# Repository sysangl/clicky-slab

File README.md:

The second in the Brick series. Although this one is called a slab cause it's way larger than the other Brick devices.

# Clicky Slab
## The big brother of the [clicky-brick](https://github.com/sysangl/clicky-brick)

A custom keyboard that would probably cause a house fire.

## Why did I make this?
I was bored, and I needed to fix my current keyboard.

## Features
This is a 86-key keyboard, which should have at least 4KRO, using KMK on a Raspberry Pi Pico. The case and keycaps are 3D printed.
It contains all the keys on a normal keyboard without a numpad and the PRINT_SCREEN key. There are an additional 5 keys on the right hand side that can be customised to do whatever you want. By default these would control the KMK keyboard layers.

# Showcase
- PCB designed in KiCad
- Case designed in FreeCAD
- Handsoldered

# BOM
- 86x Cherry MX Switches
- 86x 1N4148 Diodes DO-35
- 86x MX Keycaps (You probably would need to 3D print them, because I randomly placed the switches :D. Would recommend a resin print to get the best feeling results)
- 1x Raspberry Pi Pico RP2040 MCU
- 1x 0.96" 192x64px OLED Display (Any Colour, I use white)
- 1x Custom Printed PCB (Gerber files are in the releases section. I use JLCPCB to manufacture my PCBs)
- 1x 3D Printed Case (Files are in the releases section)
- 3x M3 Screws
- 3x Brass Heat-Set Inserts

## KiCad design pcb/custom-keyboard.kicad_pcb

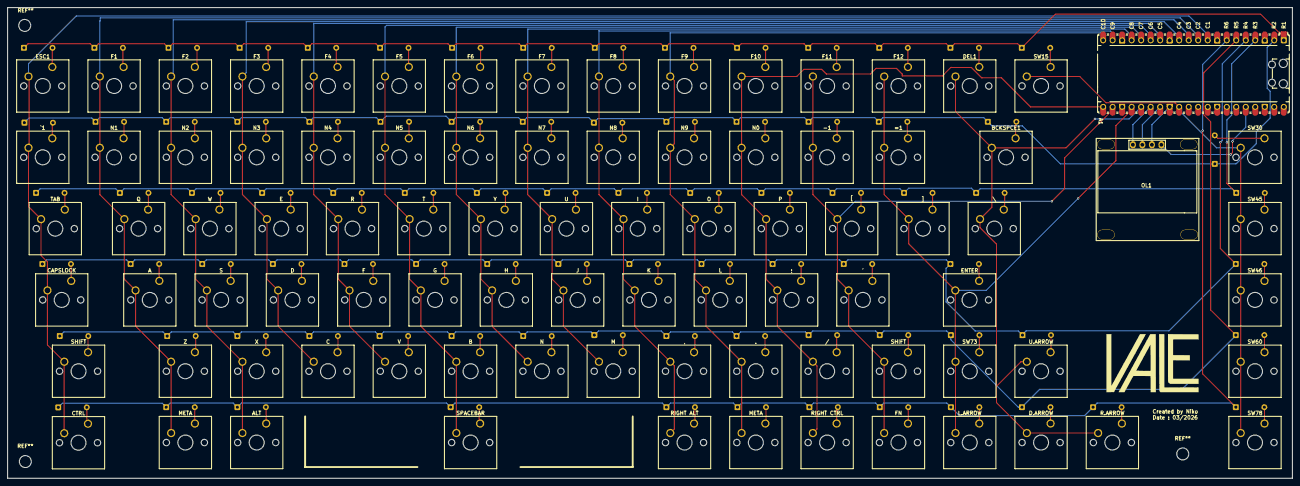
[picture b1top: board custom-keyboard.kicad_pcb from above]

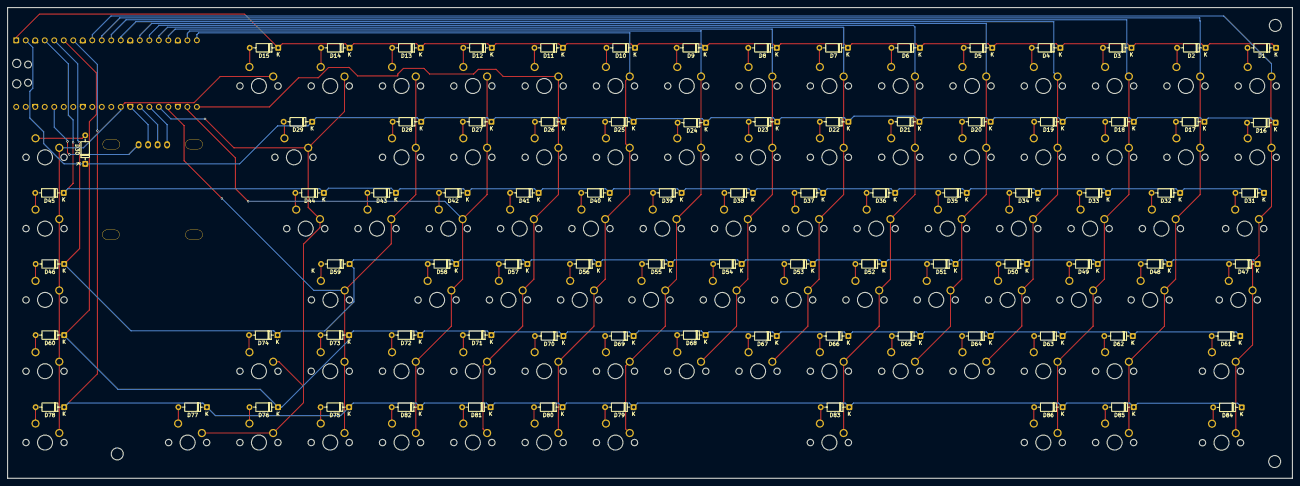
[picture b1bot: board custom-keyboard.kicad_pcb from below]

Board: 2 copper layers, 343.2 x 125.8 mm, 174 parts (86 on the bottom side), 111 nets.

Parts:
': SW_PUSH; SW_Cherry_MX_1.00u_PCB
,: SW_PUSH; SW_Cherry_MX_1.00u_PCB
-1: SW_PUSH; SW_Cherry_MX_1.00u_PCB
.: SW_PUSH; SW_Cherry_MX_1.00u_PCB
/: SW_PUSH; SW_Cherry_MX_1.00u_PCB
;: SW_PUSH; SW_Cherry_MX_1.00u_PCB
=1: SW_PUSH; SW_Cherry_MX_1.00u_PCB
A: SW_PUSH; SW_Cherry_MX_1.00u_PCB
A1: RaspberryPi_Pico; RaspberryPi_Pico_Common_Unspecified
ALT: SW_PUSH; SW_Cherry_MX_1.00u_PCB
B: SW_PUSH; SW_Cherry_MX_1.00u_PCB
BCKSPCE1: SW_PUSH; SW_Cherry_MX_1.00u_PCB
C: SW_PUSH; SW_Cherry_MX_1.00u_PCB
CAPSLOCK: SW_PUSH; SW_Cherry_MX_1.00u_PCB
CTRL: SW_PUSH; SW_Cherry_MX_1.00u_PCB
D, D.ARROW: SW_PUSH; SW_Cherry_MX_1.00u_PCB
D1, D2, D3, D4, D5, D6, D7, D8, D9, D10, D11, D12, D13, D14, D15, D16, D17, D18, D19, D20, D21, D22, D23, D24, D25, D26, D27, D28, D29, D30, D31, D32, D33, D34, D35, D36, D37, D38, D39, D40, D41, D42, D43, D44, D45, D46, D47, D48, D49, D50, D51, D52, D53, D54, D55, D56, D57, D58, D59, D60, D61, D62, D63, D64, D65, D66, D67, D68, D69, D70, D71, D72, D73, D74, D75, D76, D77, D78, D79, D80, D81, D82, D83, D84, D85, D86: 1N4148; D_DO-35_SOD27_P7.62mm_Horizontal
DEL1: SW_PUSH; SW_Cherry_MX_1.00u_PCB
E: SW_PUSH; SW_Cherry_MX_1.00u_PCB
ENTER: SW_PUSH; SW_Cherry_MX_1.00u_PCB
ESC1: SW_PUSH; SW_Cherry_MX_1.00u_PCB
F, F1, F2, F3, F4, F5, F6, F7, F8, F9, F10, F11, F12: SW_PUSH; SW_Cherry_MX_1.00u_PCB
FN: SW_PUSH; SW_Cherry_MX_1.00u_PCB
G: SW_PUSH; SW_Cherry_MX_1.00u_PCB
H: SW_PUSH; SW_Cherry_MX_1.00u_PCB
I: SW_PUSH; SW_Cherry_MX_1.00u_PCB
J: SW_PUSH; SW_Cherry_MX_1.00u_PCB
K: SW_PUSH; SW_Cherry_MX_1.00u_PCB
L, L.ARROW: SW_PUSH; SW_Cherry_MX_1.00u_PCB
M: SW_PUSH; SW_Cherry_MX_1.00u_PCB
META: SW_PUSH; SW_Cherry_MX_1.00u_PCB
META#2: SW_PUSH; SW_Cherry_MX_1.00u_PCB
N, N0, N1, N2, N3, N4, N5, N6, N7, N8, N9: SW_PUSH; SW_Cherry_MX_1.00u_PCB
O: SW_PUSH; SW_Cherry_MX_1.00u_PCB
OL1: OLED; 128x64OLED
P: SW_PUSH; SW_Cherry_MX_1.00u_PCB
Q: SW_PUSH; SW_Cherry_MX_1.00u_PCB
R, R.ARROW: SW_PUSH; SW_Cherry_MX_1.00u_PCB
RIGHT ALT: SW_PUSH; SW_Cherry_MX_1.00u_PCB
RIGHT CTRL: SW_PUSH; SW_Cherry_MX_1.00u_PCB
S: SW_PUSH; SW_Cherry_MX_1.00u_PCB
SHIFT: SW_PUSH; SW_Cherry_MX_1.00u_PCB
SHIFT#2: SW_PUSH; SW_Cherry_MX_1.00u_PCB
SPACEBAR: SW_PUSH; SW_Cherry_MX_1.00u_PCB
SW15, SW30, SW45, SW46, SW60, SW73, SW78: SW_PUSH; SW_Cherry_MX_1.00u_PCB
T: SW_PUSH; SW_Cherry_MX_1.00u_PCB
TAB: SW_PUSH; SW_Cherry_MX_1.00u_PCB
U, U.ARROW: SW_PUSH; SW_Cherry_MX_1.00u_PCB
V: SW_PUSH; SW_Cherry_MX_1.00u_PCB
W: SW_PUSH; SW_Cherry_MX_1.00u_PCB
X: SW_PUSH; SW_Cherry_MX_1.00u_PCB
Y: SW_PUSH; SW_Cherry_MX_1.00u_PCB
Z: SW_PUSH; SW_Cherry_MX_1.00u_PCB
[: SW_PUSH; SW_Cherry_MX_1.00u_PCB
\: SW_PUSH; SW_Cherry_MX_1.00u_PCB
]: SW_PUSH; SW_Cherry_MX_1.00u_PCB
`1: SW_PUSH; SW_Cherry_MX_1.00u_PCB

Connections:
COL1: A1.9 (GPIO6), CAPSLOCK.2, CTRL.2, ESC1.2, SHIFT.2, TAB.2, `1.2
COL2: A.2, A1.10 (GPIO7), F1.2, META.2, N1.2, Q.2, Z.2
COL3: A1.11 (GPIO8), ALT.2, F2.2, N2.2, S.2, W.2, X.2
COL4: A1.12 (GPIO9), C.2, D.2, E.2, F3.2, N3.2
COL5: A1.14 (GPIO10), F.2, F4.2, N4.2, R.2, V.2
COL6: A1.15 (GPIO11), B.2, F5.2, G.2, N5.2, SPACEBAR.2, T.2
COL7: A1.16 (GPIO12), F6.2, H.2, N.2, N6.2, Y.2
COL8: A1.17 (GPIO13), F7.2, J.2, M.2, N7.2, U.2
COL9: ,.2, A1.19 (GPIO14), F8.2, I.2, K.2, N8.2, RIGHT ALT.2
COL10: ..2, A1.20 (GPIO15), F9.2, L.2, META#2.2, N9.2, O.2
COL11: /.2, ;.2, A1.21 (GPIO16), F10.2, N0.2, P.2, RIGHT CTRL.2
COL12: '.2, -1.2, A1.22 (GPIO17), F11.2, FN.2, SHIFT#2.2, [.2
COL13: =1.2, A1.24 (GPIO18), ENTER.2, F12.2, L.ARROW.2, SW73.2, ].2
COL14: A1.25 (GPIO19), BCKSPCE1.2, D.ARROW.2, DEL1.2, R.ARROW.2, U.ARROW.2, \.2
COL15: A1.29 (GPIO22), SW15.2, SW30.2, SW45.2, SW46.2, SW60.2, SW78.2
GND: A1.3 (GND), A1.8 (GND), A1.13 (GND), A1.18 (GND), A1.23 (GND), A1.28 (GND), A1.38 (GND), OL1.3 (GND)
unnamed: D1.2 (A), ESC1.1
unnamed: D2.2 (A), F1.1
unnamed: D3.2 (A), F2.1
unnamed: D4.2 (A), F3.1
unnamed: D5.2 (A), F4.1
unnamed: D6.2 (A), F5.1
unnamed: D7.2 (A), F6.1
unnamed: D8.2 (A), F7.1
unnamed: D9.2 (A), F8.1
unnamed: D10.2 (A), F9.1
unnamed: D11.2 (A), F10.1
unnamed: D12.2 (A), F11.1
unnamed: D13.2 (A), F12.1
unnamed: D14.2 (A), DEL1.1
unnamed: D15.2 (A), SW15.1
unnamed: D16.2 (A), `1.1
unnamed: D17.2 (A), N1.1
unnamed: D18.2 (A), N2.1
unnamed: D19.2 (A), N3.1
unnamed: D20.2 (A), N4.1
unnamed: D21.2 (A), N5.1
unnamed: D22.2 (A), N6.1
unnamed: D23.2 (A), N7.1
unnamed: D24.2 (A), N8.1
unnamed: D25.2 (A), N9.1
unnamed: D26.2 (A), N0.1
unnamed: -1.1, D27.2 (A)
unnamed: =1.1, D28.2 (A)
unnamed: BCKSPCE1.1, D29.2 (A)
unnamed: D30.2 (A), SW30.1
unnamed: D31.2 (A), TAB.1
unnamed: D32.2 (A), Q.1
unnamed: D33.2 (A), W.1
unnamed: D34.2 (A), E.1
unnamed: D35.2 (A), R.1
unnamed: D36.2 (A), T.1
unnamed: D37.2 (A), Y.1
unnamed: D38.2 (A), U.1
unnamed: D39.2 (A), I.1
unnamed: D40.2 (A), O.1
unnamed: D41.2 (A), P.1
unnamed: D42.2 (A), [.1
unnamed: D43.2 (A), ].1
unnamed: D44.2 (A), \.1
unnamed: D45.2 (A), SW45.1
unnamed: D46.2 (A), SW46.1
unnamed: CAPSLOCK.1, D47.2 (A)
unnamed: A.1, D48.2 (A)
unnamed: D49.2 (A), S.1
unnamed: D.1, D50.2 (A)
unnamed: D51.2 (A), F.1
unnamed: D52.2 (A), G.1
unnamed: D53.2 (A), H.1
unnamed: D54.2 (A), J.1
unnamed: D55.2 (A), K.1
unnamed: D56.2 (A), L.1
unnamed: ;.1, D57.2 (A)
unnamed: '.1, D58.2 (A)
unnamed: D59.2 (A), ENTER.1
unnamed: D60.2 (A), SW60.1
unnamed: D61.2 (A), SHIFT.1
unnamed: D62.2 (A), Z.1
unnamed: D63.2 (A), X.1
unnamed: C.1, D64.2 (A)
unnamed: D65.2 (A), V.1
unnamed: B.1, D66.2 (A)
unnamed: D67.2 (A), N.1
unnamed: D68.2 (A), M.1
unnamed: ,.1, D69.2 (A)
unnamed: ..1, D70.2 (A)
unnamed: /.1, D71.2 (A)
unnamed: D72.2 (A), SHIFT#2.1
unnamed: D73.2 (A), SW73.1
unnamed: D74.2 (A), U.ARROW.1
unnamed: D75.2 (A), L.ARROW.1
unnamed: D76.2 (A), D.ARROW.1
unnamed: D77.2 (A), R.ARROW.1
unnamed: D78.2 (A), SW78.1
unnamed: D79.2 (A), RIGHT ALT.1
unnamed: D80.2 (A), META#2.1
unnamed: D81.2 (A), RIGHT CTRL.1
unnamed: D82.2 (A), FN.1
unnamed: D83.2 (A), SPACEBAR.1
unnamed: CTRL.1, D84.2 (A)
unnamed: D85.2 (A), META.1
unnamed: ALT.1, D86.2 (A)
OLED SCL: A1.27 (GPIO21), OL1.2 (SCL)
OLED SDA: A1.26 (GPIO20), OL1.1 (SDA)
ROW1: A1.1 (GPIO0), D1.1 (K), D2.1 (K), D3.1 (K), D4.1 (K), D5.1 (K), D6.1 (K), D7.1 (K), D8.1 (K), D9.1 (K), D10.1 (K), D11.1 (K), D12.1 (K), D13.1 (K), D14.1 (K), D15.1 (K)
ROW2: A1.2 (GPIO1), D16.1 (K), D17.1 (K), D18.1 (K), D19.1 (K), D20.1 (K), D21.1 (K), D22.1 (K), D23.1 (K), D24.1 (K), D25.1 (K), D26.1 (K), D27.1 (K), D28.1 (K), D29.1 (K), D30.1 (K)
ROW3: A1.4 (GPIO2), D31.1 (K), D32.1 (K), D33.1 (K), D34.1 (K), D35.1 (K), D36.1 (K), D37.1 (K), D38.1 (K), D39.1 (K), D40.1 (K), D41.1 (K), D42.1 (K), D43.1 (K), D44.1 (K), D45.1 (K)
ROW4: A1.5 (GPIO3), D46.1 (K), D47.1 (K), D48.1 (K), D49.1 (K), D50.1 (K), D51.1 (K), D52.1 (K), D53.1 (K), D54.1 (K), D55.1 (K), D56.1 (K), D57.1 (K), D58.1 (K), D59.1 (K), D74.1 (K)
ROW5: A1.6 (GPIO4), D60.1 (K), D61.1 (K), D62.1 (K), D63.1 (K), D64.1 (K), D65.1 (K), D66.1 (K), D67.1 (K), D68.1 (K), D69.1 (K), D70.1 (K), D71.1 (K), D72.1 (K), D73.1 (K), D76.1 (K)
ROW6: A1.7 (GPIO5), D75.1 (K), D77.1 (K), D78.1 (K), D79.1 (K), D80.1 (K), D81.1 (K), D82.1 (K), D83.1 (K), D84.1 (K), D85.1 (K), D86.1 (K)
VCC: A1.36 (3V3), OL1.4 (VCC)

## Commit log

2026-03-03 Initiliase Repo
2026-03-03 updating directory structure
2026-03-03 Started work on the case, updated a bit of the ReadMe
2026-03-03 Added basic keyboard code to firmware
